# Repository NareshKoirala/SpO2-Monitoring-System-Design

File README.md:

# SpO2-Monitoring-System-Design

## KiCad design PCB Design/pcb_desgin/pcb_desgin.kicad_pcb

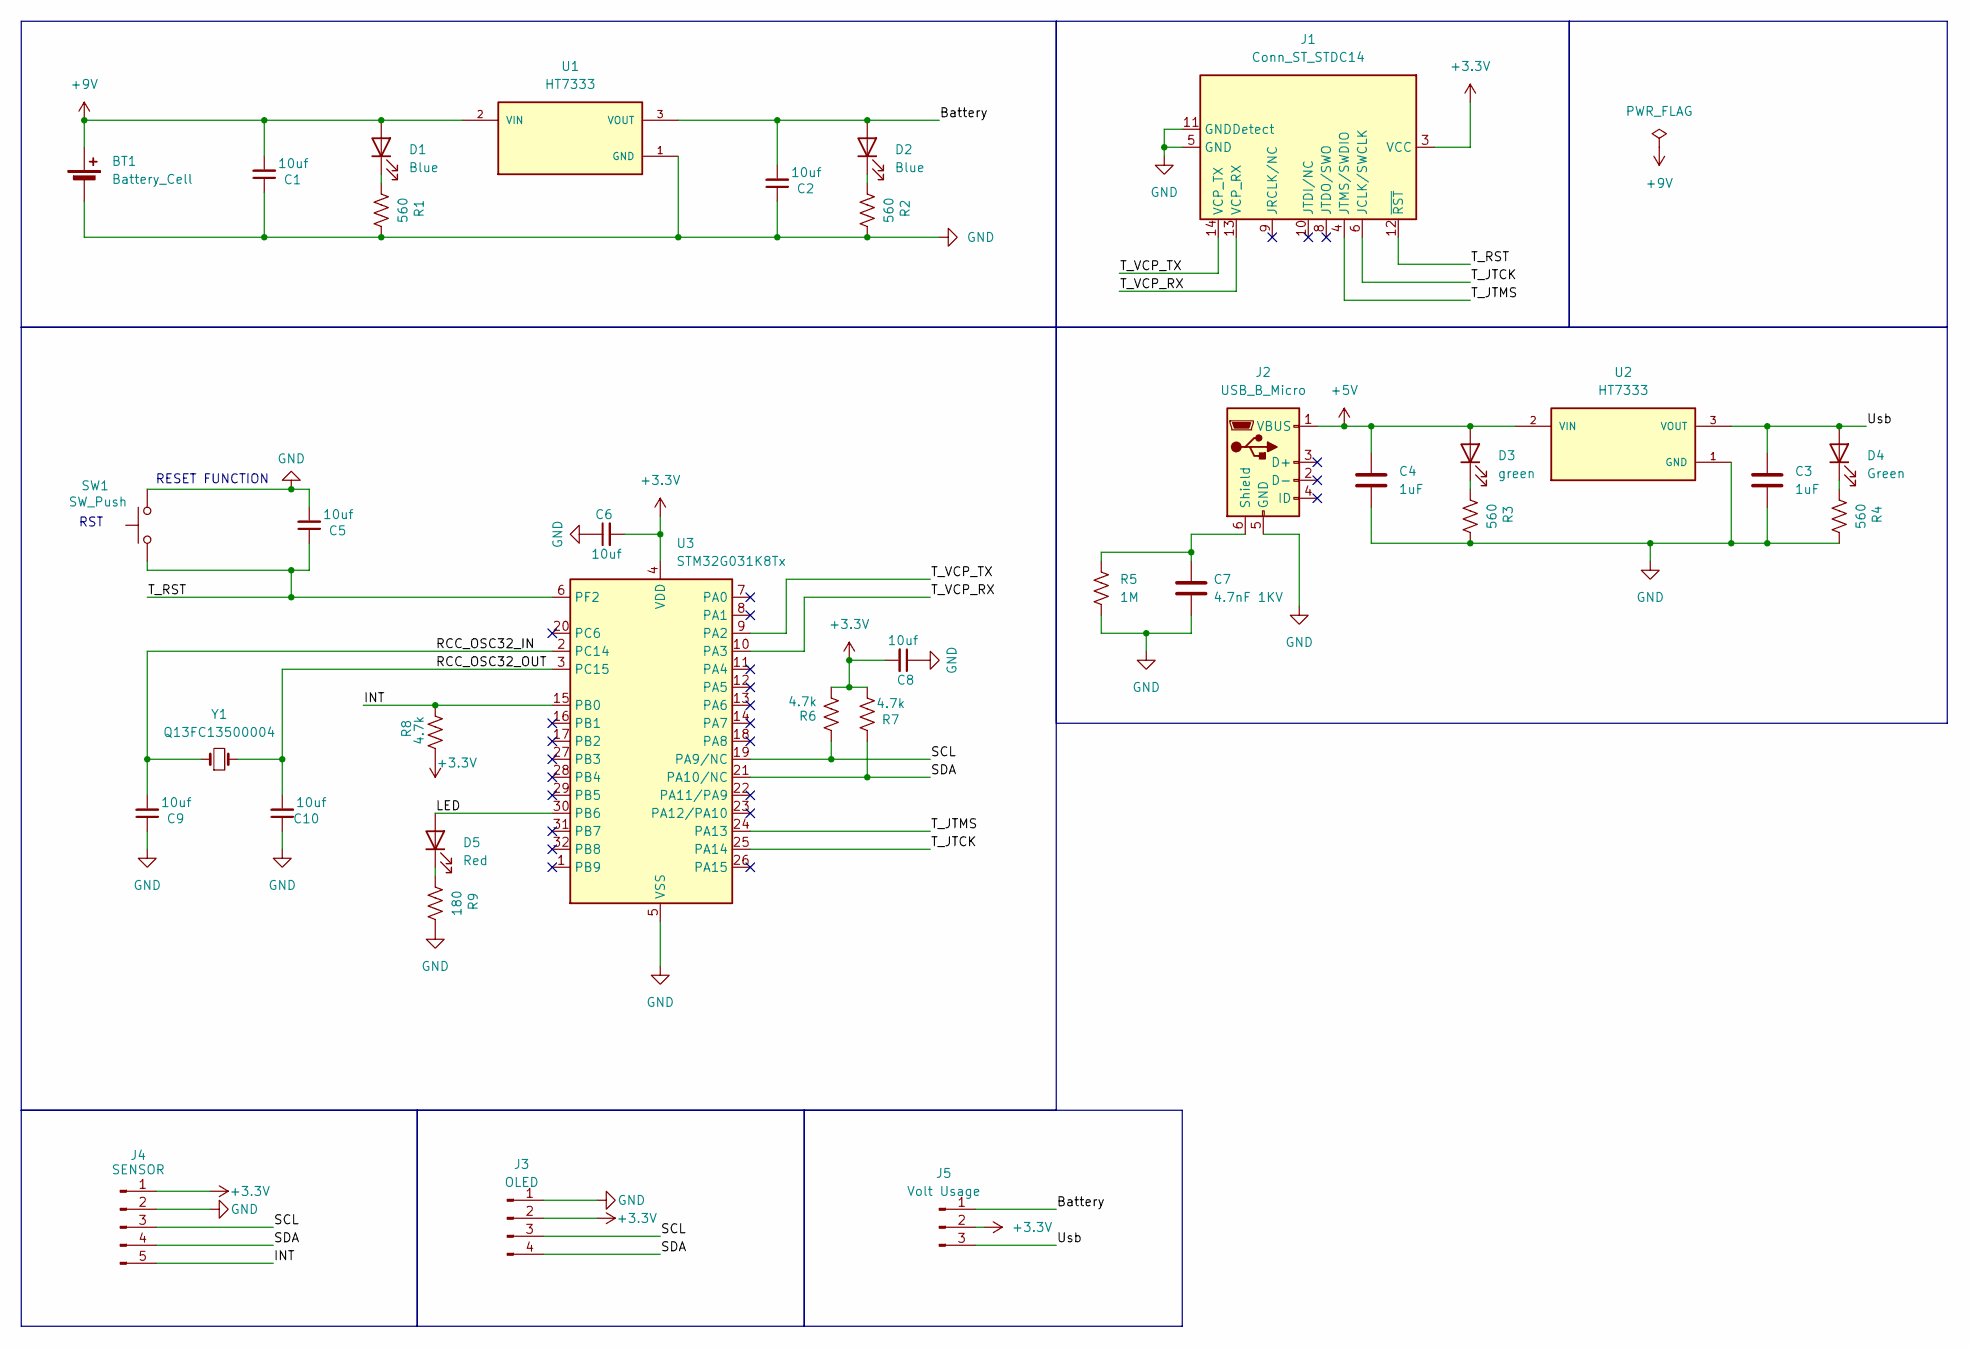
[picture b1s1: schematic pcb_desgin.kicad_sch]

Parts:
BT1: Battery_Cell; BatteryHolder_Eagle_12BH611-GR
C1, C2, C5, C6, C8, C9, C10: 10uf; C_0603_1608Metric
C3, C4: 1uF; C_0603_1608Metric
C7: 4.7nF 1KV; C_0603_1608Metric
D1, D2: Blue; LED_0603_1608Metric
D3: green; LED_0603_1608Metric
D4: Green; LED_0603_1608Metric
D5: Red; LED_0603_1608Metric
J1: Conn_ST_STDC14; 3220-14-0100-00; ManPartN 3220-14-0100-00
J2: USB_B_Micro; USB_Micro-B_Amphenol_10118194_Horizontal
J3: OLED; PinHeader_1x04_P2.54mm_Vertical
J4: SENSOR; PinHeader_1x05_P2.54mm_Vertical
J5: Volt Usage; PinHeader_1x03_P2.54mm_Vertical
R1, R2, R3, R4: 560; R_0603_1608Metric
R5: 1M; R_0603_1608Metric
R6, R7, R8: 4.7k; R_0603_1608Metric
R9: 180; R_0603_1608Metric
SW1: SW_Push; SW_PUSH_6mm_H4.3mm
U1, U2: HT7333; IC_HT7333; PARTREV 1.80
U3: STM32G031K8Tx; LQFP-32
Y1: Q13FC13500004; FC135327680KAE3

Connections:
+3.3V: C6.2, C8.2, J1.3 (VCC), J3.2, J4.1, J5.2, R6.2, R7.2, R8.2, U3.4 (VDD)
+5V: C4.1, D3.2 (A), J2.1 (VBUS), U2.2 (VIN)
+9V: BT1.1 (+), C1.2, D1.2 (A), U1.2 (VIN)
/Battery: C2.2, D2.2 (A), J5.1, U1.3 (VOUT)
/INT: J4.5, R8.1, U3.15 (PB0)
/LED: D5.2 (A), U3.30 (PB6)
/RCC_OSC32_IN: C9.2, U3.2 (PC14), Y1.1
/RCC_OSC32_OUT: C10.2, U3.3 (PC15), Y1.2
/SCL: J3.3, J4.3, R6.1, U3.19 (PA9/NC)
/SDA: J3.4, J4.4, R7.1, U3.21 (PA10/NC)
/T_JTCK: J1.6 (JCLK/SWCLK), U3.25 (PA14)
/T_JTMS: J1.4 (JTMS/SWDIO), U3.24 (PA13)
/T_RST: C5.1, J1.12 (~RST), SW1.1, U3.6 (PF2)
/T_VCP_RX: J1.13 (VCP_RX), U3.10 (PA3)
/T_VCP_TX: J1.14 (VCP_TX), U3.9 (PA2)
/Usb: C3.1, D4.2 (A), J5.3, U2.3 (VOUT)
GND: BT1.2 (-), C1.1, C2.1, C3.2, C4.2, C5.2, C6.1, C7.2, C8.1, C9.1, C10.1, J1.5 (GND), J1.7 (GND), J1.11 (GNDDetect), J2.5 (GND), J3.1, J4.2, R1.1, R2.1, R3.1, R4.1, R5.2, R9.1, SW1.2, U1.1 (GND), U2.1 (GND), U3.5 (VSS)
unnamed: D1.1 (K), R1.2
unnamed: D2.1 (K), R2.2
unnamed: D3.1 (K), R3.2
unnamed: D4.1 (K), R4.2
unnamed: D5.1 (K), R9.2
unnamed: C7.1, J2.6 (Shield), R5.1

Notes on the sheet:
RST
RESET FUNCTION

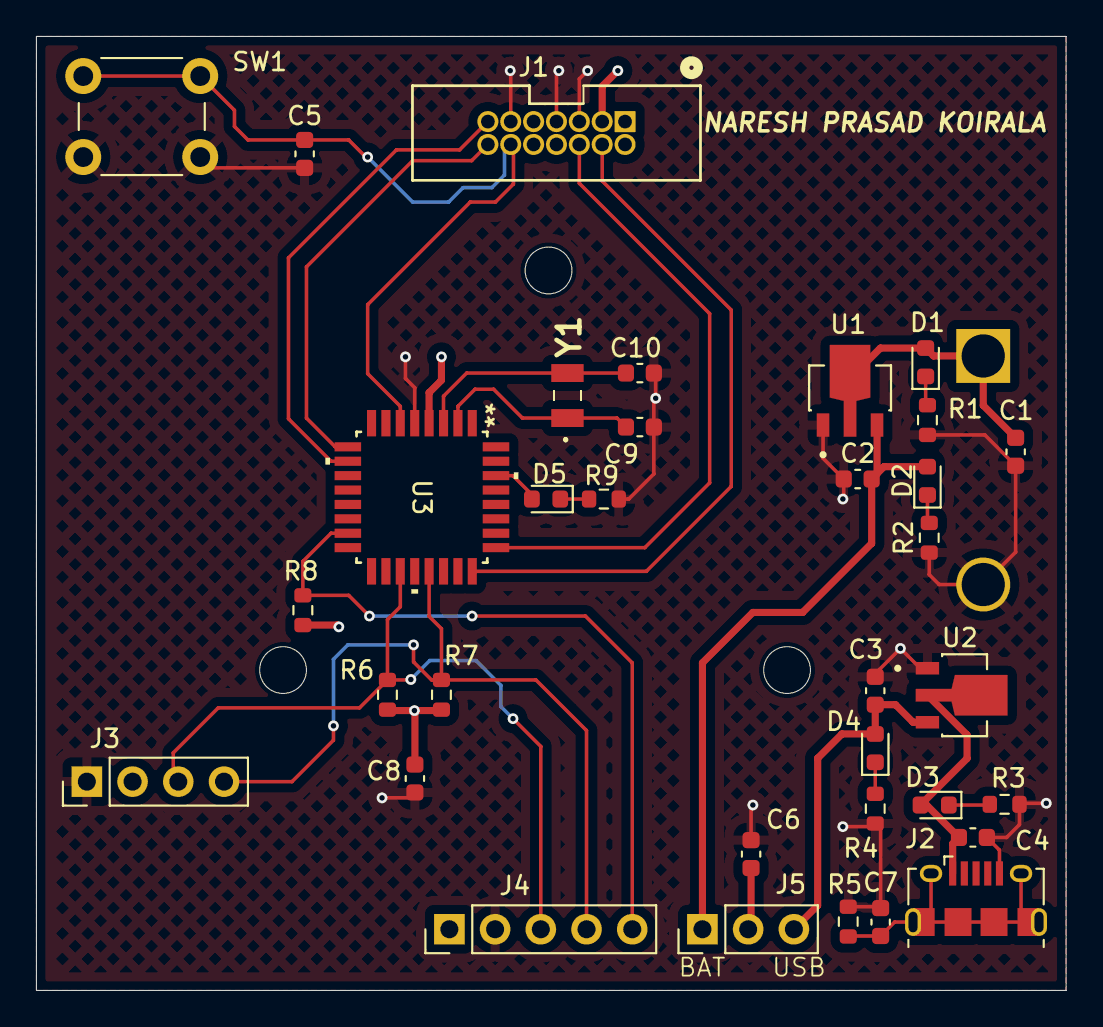
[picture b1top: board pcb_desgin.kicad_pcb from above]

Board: 4 copper layers, 57.2 x 53.0 mm, 35 parts (1 on the bottom side), 23 nets.

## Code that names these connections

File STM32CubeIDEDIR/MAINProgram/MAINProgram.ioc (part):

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Mcu.Name=STM32G031K(4-6-8)Tx
Mcu.Package=LQFP32
Mcu.UserName=STM32G031K8Tx
PA10.Mode=I2C
PA10.Signal=I2C1_SDA
PA13.GPIOParameters=GPIO_Label
PA13.GPIO_Label=T_JTMS
PA13.Mode=Serial_Wire
PA13.Signal=SYS_SWDIO
PA14-BOOT0.GPIOParameters=GPIO_Label
PA14-BOOT0.GPIO_Label=T_JTCK
PA14-BOOT0.Mode=Serial_Wire
PA14-BOOT0.Signal=SYS_SWCLK
PA2.GPIOParameters=GPIO_PuPd,GPIO_Label
PA2.GPIO_Label=T_VCP_TX
PA2.GPIO_PuPd=GPIO_PULLUP
PA2.Mode=Asynchronous
PA2.Signal=USART2_TX
PA3.GPIOParameters=GPIO_PuPd,GPIO_Label
PA3.GPIO_Label=T_VCP_RX
PA3.GPIO_PuPd=GPIO_PULLUP
PA3.Mode=Asynchronous
PA3.Signal=USART2_RX
PA9.Mode=I2C
PA9.Signal=I2C1_SCL
PB0.GPIOParameters=GPIO_PuPd,GPIO_Label,GPIO_ModeDefaultEXTI
PB0.GPIO_Label=Int_
PB0.GPIO_ModeDefaultEXTI=GPIO_MODE_IT_FALLING
PB0.GPIO_PuPd=GPIO_PULLUP
PB0.Signal=GPXTI0
PB6.Signal=GPIO_Output
PC14-OSC32_IN\ (PC14).Mode=LSE-External-Oscillator
PC14-OSC32_IN\ (PC14).Signal=RCC_OSC32_IN
PC15-OSC32_OUT\ (PC15).Mode=LSE-External-Oscillator
PC15-OSC32_OUT\ (PC15).Signal=RCC_OSC32_OUT
PC6.GPIOParameters=GPIO_Label
PC6.GPIO_Label=LD3 [Green]
PC6.Signal=GPIO_Output
PF2\ -\ NRST.GPIOParameters=GPIO_Label,GPIO_ModeDefaultEXTI
PF2\ -\ NRST.GPIO_Label=T_NRST
PF2\ -\ NRST.GPIO_ModeDefaultEXTI=GPIO_MODE_IT_RISING
PF2\ -\ NRST.Signal=GPXTI2
RCC.HSE_VALUE=8000000
RCC.SYSCLKFreq_VALUE=16000000
board=NUCLEO-G031K8
boardIOC=true

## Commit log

2025-08-12 Transfering to this public repo
